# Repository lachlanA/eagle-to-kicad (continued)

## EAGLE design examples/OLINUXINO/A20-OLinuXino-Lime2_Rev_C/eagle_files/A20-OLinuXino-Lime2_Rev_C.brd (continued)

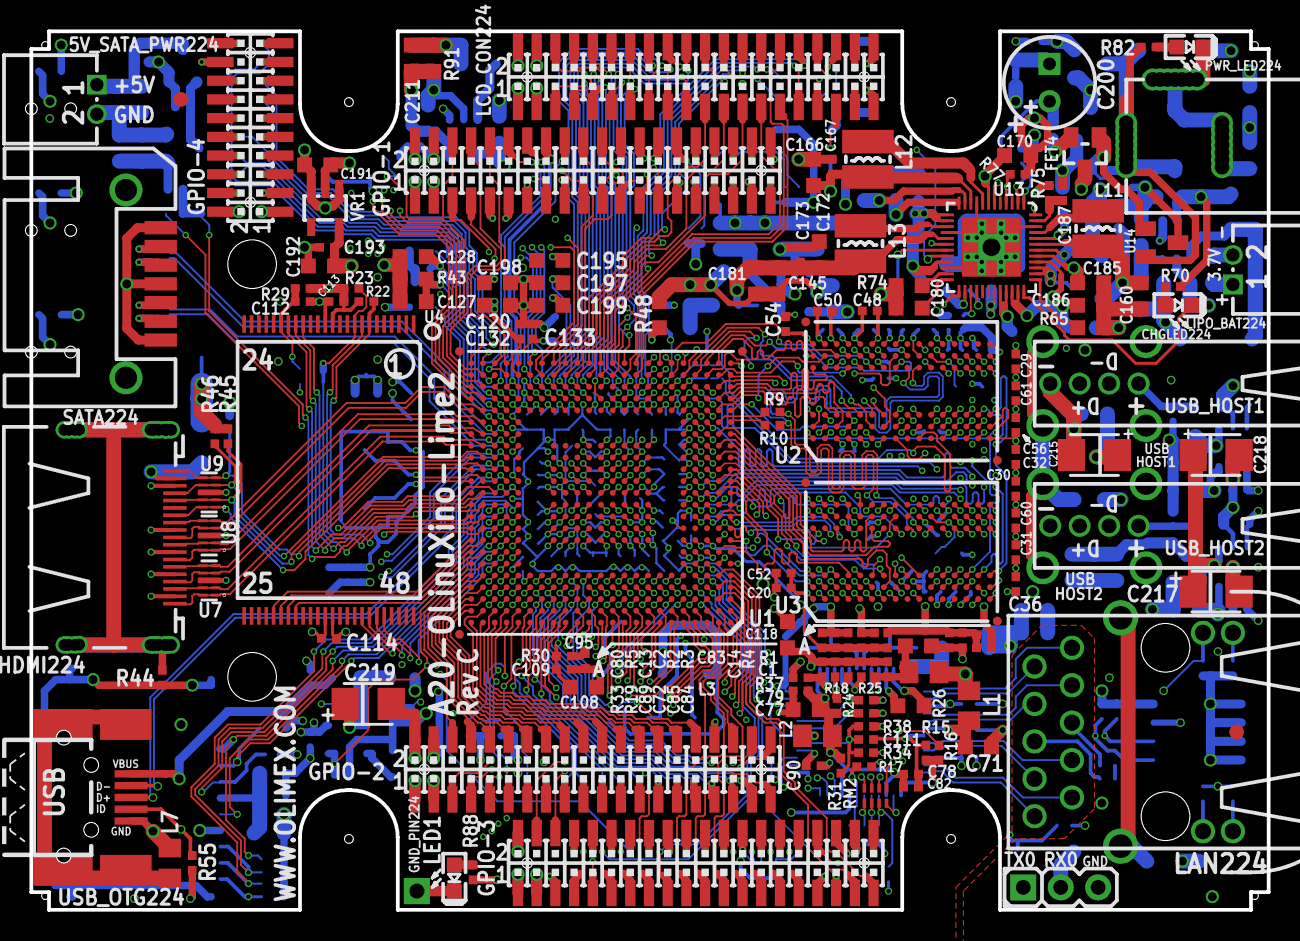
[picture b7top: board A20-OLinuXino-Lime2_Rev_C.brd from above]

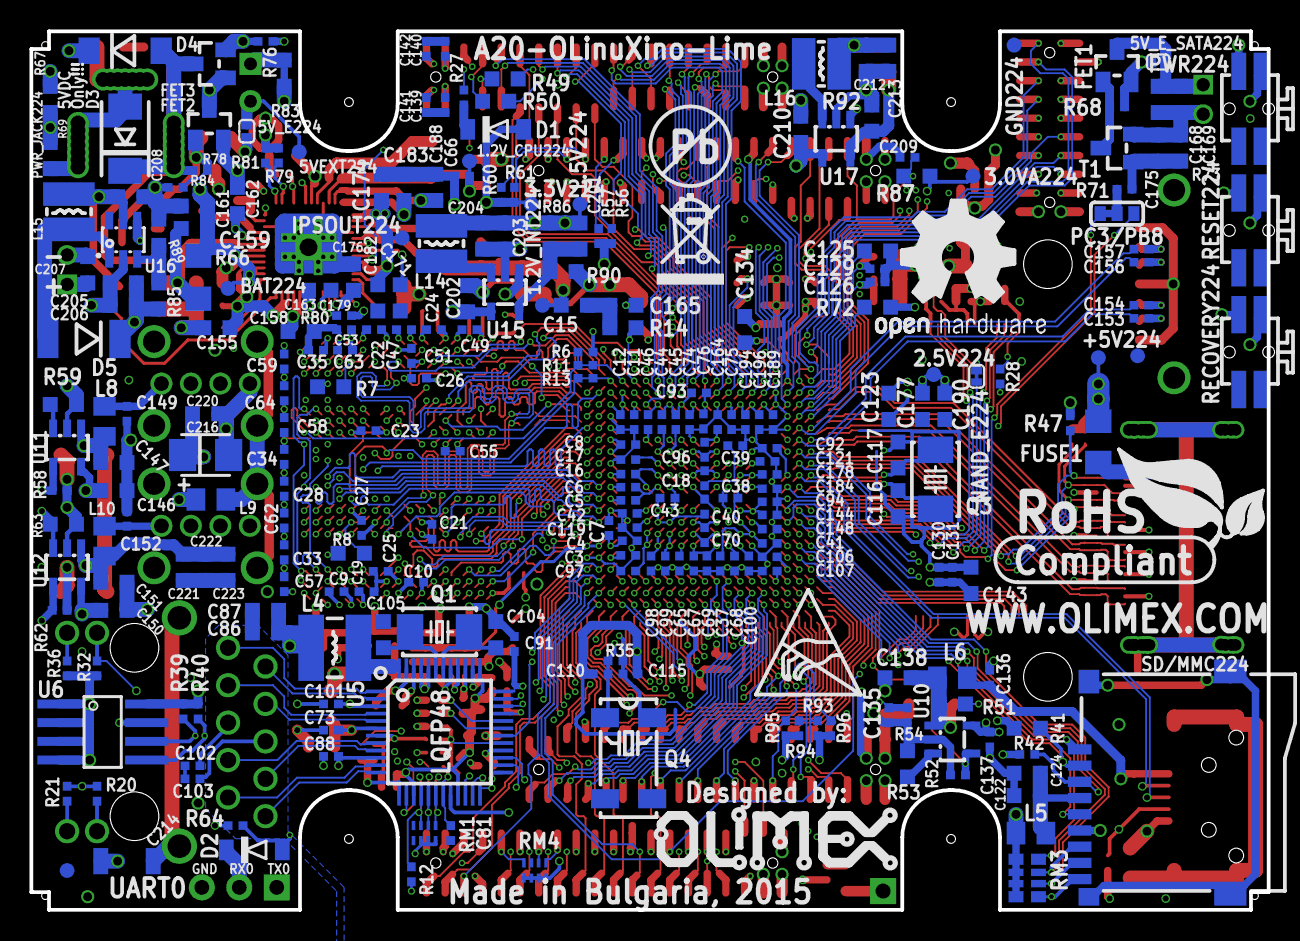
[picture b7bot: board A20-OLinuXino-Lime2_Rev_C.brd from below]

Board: 8 copper layers, 84.0 x 59.6 mm, 420 parts (274 on the bottom side), 423 nets.

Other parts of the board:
U$2: HAMMOND_1593LBK_A10_LIME
U$5: LOGO-OPENHARDWARE_8X8
U$6: OLIMEX1_V
U$9: PB
U$10: ESD_SYMBOL
U$11: RECYCLE_BIN1/8
U$12: ROHS

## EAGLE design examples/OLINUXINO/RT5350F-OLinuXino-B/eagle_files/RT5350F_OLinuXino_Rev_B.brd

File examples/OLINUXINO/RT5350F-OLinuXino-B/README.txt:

NOTE: ***** USE AT YOUR OWN RISK *****

This contains the eagle file's from OLIMEX/OLINUXINO from github, which have been Renumbered to work with KiCad
as KiCad will not work correctly with out parts reference ending in a number.
Also note the Eagle files have been converted to version 6.xx of eagle.

source of this project example is at Github address:
  OLINUXINO/HARDWARE/RT5350F/RT5350F-OLinuXino/RT5350F-OLinuXino-B/

The following is the error report. for lib extraction from the eagle sch/pcb to a eagle lbr.
which is then converted in to KiCad format.

#**** LOG Errors Start ****#
ERROR: package name:CD42(43)  Has Bad/illegal charter in it's package Alisa name!
   Package Alaise  Name:-CD42(43)
   Error Postion & Char:     (  )
   Bad charter(s) have been replaced with  '_'  This MAY FIX OR, CAUSE MORE ERROR'S! Plese fix the Alias!
ERROR: package name:CD52(53)  Has Bad/illegal charter in it's package Alisa name!
   Package Alaise  Name:-CD52(53)
   Error Postion & Char:     (  )
   Bad charter(s) have been replaced with  '_'  This MAY FIX OR, CAUSE MORE ERROR'S! Plese fix the Alias!
ERROR: package name:CD73(75)  Has Bad/illegal charter in it's package Alisa name!
   Package Alaise  Name:-CD73(75)
   Error Postion & Char:     (  )
   Bad charter(s) have been replaced with  '_'  This MAY FIX OR, CAUSE MORE ERROR'S! Plese fix the Alias!
ERROR: package name:ML26-MALE(GBH-254-SMT-26)  Has Bad/illegal charter in it's package Alisa name!
   Package Alaise  Name:-(GBH-254-SMT-26)
   Error Postion & Char: (              )
   Bad charter(s) have been replaced with  '_'  This MAY FIX OR, CAUSE MORE ERROR'S! Plese fix the Alias!
ERROR: package name:F-V50X-2X13-LF  Has Bad/illegal charter in it's package Alisa name!
   Package Alaise  Name:-F-V50X-2X13-LF(FEMALE)
   Error Postion & Char:               (      )
   Bad charter(s) have been replaced with  '_'  This MAY FIX OR, CAUSE MORE ERROR'S! Plese fix the Alias!

#**** LOG Warning Start ****#
WARNING: Over lapping Pin(s) on SYMBOL:WIFI_RF
   Pin =GND_2

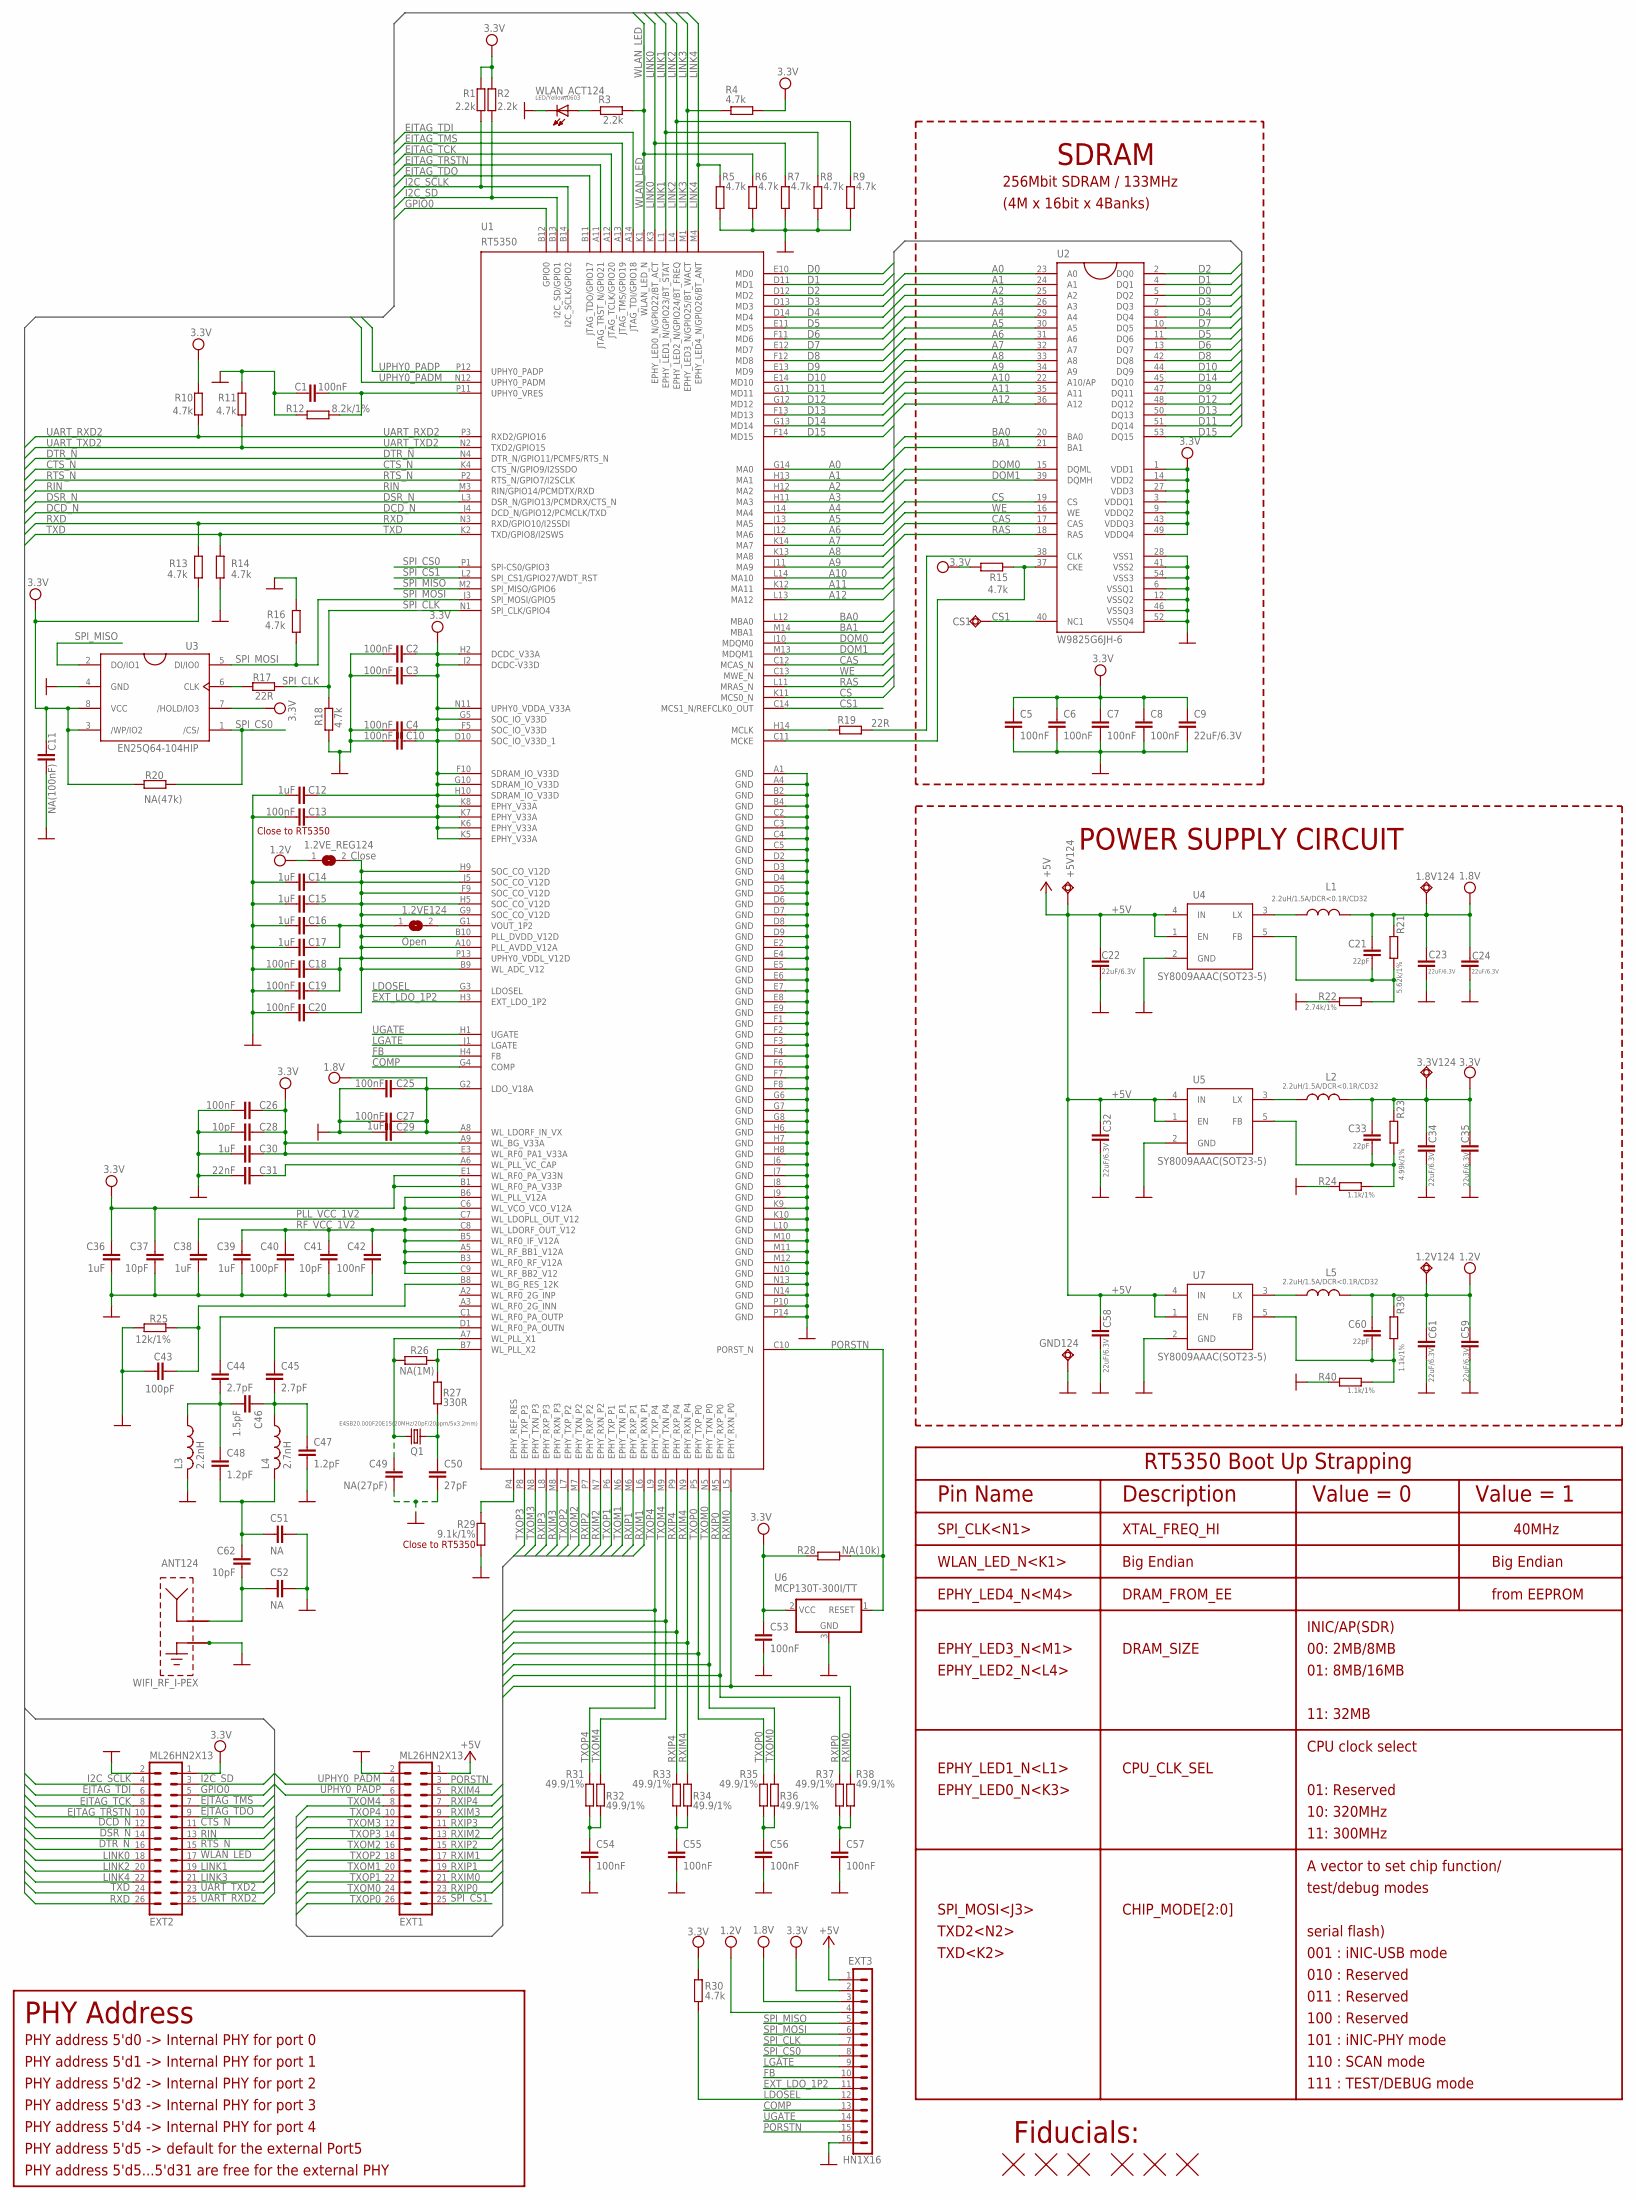
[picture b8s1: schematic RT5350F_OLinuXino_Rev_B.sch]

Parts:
1.2V124, 1.8V124: TESTPADTESTPAD_40-ROUND; TESTPAD_40-ROUND
1.2VE124: Open; SJ_1_SMALLER
1.2VE_REG124: Close; SJ_1_SMALLER
3.3V124: 3.3V; TESTPAD_40-ROUND
+5V124: TESTPADTESTPAD_40-ROUND; TESTPAD_40-ROUND
ANT124: WIFI_RF_I-PEX; WIFI_RF
C1, C2, C3, C4, C5, C6, C7, C8, C10, C13, C18, C19, C20, C25, C26, C27, C42, C53, C54, C55, C56, C57: 100nF; C0402_TI
C9, C22, C23, C24, C32, C34, C35, C58, C59, C61: 22uF/6.3V; C0603_DWS
C11: NA(100nF); C0402_TI
C12, C14, C15, C16, C17, C29, C30, C36, C38, C39: 1uF; C0603_DWS
C21, C33, C60: 22pF; C0603_DWS
C28, C37, C41, C62: 10pF; C0402_TI
C31: 22nF; C0402_TI
C40, C43: 100pF; C0402_TI
C44, C45: 2.7pF; C0402_TI
C46: 1.5pF; C0402_TI
C47, C48: 1.2pF; C0402_TI
C49: NA(27pF); C0603_DWS
C50: 27pF; C0603_DWS
C51, C52: NA; C0402_TI
CS1: TESTPADTESTPAD30/30; TESTPAD_30-ROUND
EXT1, EXT2: ML26HN2X13; HN2X13-MALE
EXT3: HN1X16
FID1, FID2, FID3, FID4, FID5, FID6: FIDUCIAL; FIDUCIAL-1X3
GND124: TESTPADTESTPAD_40-ROUND; TESTPAD_40-ROUND
L1, L2, L5: 2.2uH/1.5A/DCR<0.1R/CD32; CD32
L3: 2.2nH; L0603_5MIL_DWS
L4: 2.7nH; L0402_TI
Q1: E4SB20.000F20E15(20MHz/20pF/20ppm/5x3.2mm); HCX-4S
R1, R2, R3: 2.2k; R0603_5MIL_DWS
R4, R5, R6, R7, R8, R9, R10, R11, R13, R14, R15, R16, R18, R30: 4.7k; R0603_5MIL_DWS
R12: 8.2k/1%; R0603_5MIL_DWS
R17, R19: 22R; R0603_5MIL_DWS
R20: NA(47k); R0603_5MIL_DWS
R21: 5.62k/1%; R0603_5MIL_DWS
R22: 2.74k/1%; R0603_5MIL_DWS
R23: 4.99k/1%; R0603_5MIL_DWS
R24, R39, R40: 1.1k/1%; R0603_5MIL_DWS
R25: 12k/1%; R0402_TI
R26: NA(1M); R0603_5MIL_DWS
R27: 330R; R0603_5MIL_DWS
R28: NA(10k); R0603_5MIL_DWS
R29: 9.1k/1%; R0603_5MIL_DWS
R31, R32, R33, R34, R35, R36, R37, R38: 49.9/1%; R0603_5MIL_DWS
U1: RT5350; TFBGA196B
U2: W9825G6JH-6; 54TSOPII
U3: EN25Q64-104HIP; SO8_ATMEL_FLASH
U4, U5, U7: SY8009AAAC(SOT23-5); SOT23-5
U6: MCP130T-300I/TT; SOT23
WLAN_ACT124: LED/Yellow/0603; LED-0603

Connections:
1.2V: 1.2VE124.1, 1.2VE_REG124.2, C14.1, C15.1, C16.1, C17.1, C18.1, C19.1, C20.1, U1.A10 (PLL_AVDD_V12A), U1.B9 (WL_ADC_V12), U1.B10 (PLL_DVDD_V12D), U1.F9 (SOC_CO_V12D), U1.G9 (SOC_CO_V12D), U1.H5 (SOC_CO_V12D), U1.H9 (SOC_CO_V12D), U1.J5 (SOC_CO_V12D), U1.P13 (UPHY0_VDDL_V12D)
+5V: +5V124.1, C22.1, C32.1, C58.1, EXT1.1, EXT3.1, U4.1 (EN), U4.4 (IN), U5.1 (EN), U5.4 (IN), U7.1 (EN), U7.4 (IN)
A0: U1.G14 (MA0), U2.23 (A0)
A1: U1.H13 (MA1), U2.24 (A1)
A2: U1.H12 (MA2), U2.25 (A2)
A3: U1.H11 (MA3), U2.26 (A3)
A4: U1.J14 (MA4), U2.29 (A4)
A5: U1.J13 (MA5), U2.30 (A5)
A6: U1.J12 (MA6), U2.31 (A6)
A7: U1.K14 (MA7), U2.32 (A7)
A8: U1.K13 (MA8), U2.33 (A8)
A9: U1.J11 (MA9), U2.34 (A9)
A10: U1.L14 (MA10), U2.22 (A10/AP)
A11: U1.K12 (MA11), U2.35 (A11)
A12: U1.L13 (MA12), U2.36 (A12)
BA0: U1.L12 (MBA0), U2.20 (BA0)
BA1: U1.M14 (MBA1), U2.21 (BA1)
CAS: U1.C12 (MCAS_N), U2.17 (CAS)
COMP: EXT3.13, U1.G4 (COMP)
CS: U1.K11 (MCS0_N), U2.19 (CS)
CS1: CS1.1, U1.C14 (MCS1_N/REFCLK0_OUT), U2.40 (NC1)
CTS_N: EXT2.11, U1.K4 (CTS_N/GPIO9/I2SSDO)
D0: U1.E10 (MD0), U2.5 (DQ2)
D1: U1.D11 (MD1), U2.4 (DQ1)
D2: U1.D12 (MD2), U2.2 (DQ0)
D3: U1.D13 (MD3), U2.7 (DQ3)
D4: U1.D14 (MD4), U2.8 (DQ4)
D5: U1.E11 (MD5), U2.11 (DQ6)
D6: U1.F11 (MD6), U2.13 (DQ7)
D7: U1.E12 (MD7), U2.10 (DQ5)
D8: U1.F12 (MD8), U2.42 (DQ8)
D9: U1.E13 (MD9), U2.47 (DQ11)
D10: U1.E14 (MD10), U2.44 (DQ9)
D11: U1.G11 (MD11), U2.51 (DQ14)
D12: U1.G12 (MD12), U2.48 (DQ12)
D13: U1.F13 (MD13), U2.50 (DQ13)
D14: U1.G13 (MD14), U2.45 (DQ10)
D15: U1.F14 (MD15), U2.53 (DQ15)
DCD_N: EXT2.12, U1.J4 (DCD_N/GPIO12/PCMCLK/TXD)
DQM0: U1.J10 (MDQM0), U2.15 (DQML)
DQM1: U1.M13 (MDQM1), U2.39 (DQMH)
DSR_N: EXT2.14, U1.L3 (DSR_N/GPIO13/PCMDRX/CTS_N)
DTR_N: EXT2.16, U1.N4 (DTR_N/GPIO11/PCMFS/RTS_N)
EJTAG_TCK: EXT2.8, U1.A12 (JTAG_TCLK/GPIO20)
EJTAG_TDI: EXT2.6, U1.A14 (JTAG_TDI/GPIO18)
EJTAG_TDO: EXT2.9, U1.B11 (JTAG_TDO/GPIO17)
EJTAG_TMS: EXT2.7, U1.A13 (JTAG_TMS/GPIO19)
EJTAG_TRSTN: EXT2.10, U1.A11 (JTAG_TRST_N/GPIO21)
EXT_LDO_1P2: EXT3.11, U1.H3 (EXT_LDO_1P2)
FB: EXT3.10, U1.H4 (FB)
GND: ANT124.GND1 (GND_1), ANT124.GND2 (GND_2), C1.2, C2.2, C3.2, C4.2, C5.2, C6.2, C7.2, C8.2, C9.2, C10.2, C11.2, C12.2, C13.2, C14.2, C15.2, C16.2, C17.2, C18.2, C19.2, C20.2, C22.2, C23.2, C24.2, C25.2, C26.2, C27.2, C28.2, C29.2, C30.2, C31.2, C32.2, C34.2, C35.2, C36.2, C37.2, C38.2, C39.2, C40.2, C41.2, C42.2, C43.2, C47.2, C49.2, C50.2, C51.2, C52.2, C53.2, C54.2, C55.2, C56.2, C57.2, C58.2, C59.2, C61.2, EXT1.2, EXT2.2, EXT3.16, GND124.1, L3.2, R5.2, R6.2, R7.2, R8.2, R9.2, R11.2, R12.2, R14.2, R16.1, R18.2, R22.2, R24.2, R25.1, R29.2, R40.2, U1.A1 (GND), U1.A4 (GND), U1.B2 (GND), U1.B4 (GND), U1.C2 (GND), U1.C3 (GND), U1.C4 (GND), U1.C5 (GND), U1.D2 (GND), U1.D3 (GND), U1.D4 (GND), U1.D5 (GND), U1.D6 (GND), U1.D7 (GND), U1.D8 (GND), U1.D9 (GND), U1.E2 (GND), U1.E4 (GND), U1.E5 (GND), U1.E6 (GND), U1.E7 (GND), U1.E8 (GND), U1.E9 (GND), U1.F1 (GND), U1.F2 (GND), U1.F3 (GND), U1.F4 (GND), U1.F6 (GND), U1.F7 (GND), U1.F8 (GND), U1.G6 (GND), U1.G7 (GND), U1.G8 (GND), U1.H6 (GND), U1.H7 (GND), U1.H8 (GND), U1.J6 (GND), U1.J7 (GND), U1.J8 (GND), U1.J9 (GND), U1.K9 (GND), U1.K10 (GND), U1.L10 (GND), U1.M10 (GND), U1.M11 (GND), U1.M12 (GND), U1.N10 (GND), U1.N13 (GND), U1.N14 (GND), U1.P10 (GND), U1.P14 (GND), U2.6 (VSSQ1), U2.12 (VSSQ2), U2.28 (VSS1), U2.41 (VSS2), U2.46 (VSSQ3), U2.52 (VSSQ4), U2.54 (VSS3), U3.4 (GND), U4.2 (GND), U5.2 (GND), U6.3 (GND), U7.2 (GND), WLAN_ACT124.C
GPIO0: EXT2.5, U1.B12 (GPIO0)
I2C_SCLK: EXT2.4, R1.1, U1.B14 (I2C_SCLK/GPIO2)
I2C_SD: EXT2.3, R2.1, U1.B13 (I2C_SD/GPIO1)
LDOSEL: EXT3.12, R30.1, U1.G3 (LDOSEL)
LGATE: EXT3.9, U1.J1 (LGATE)
LINK0: EXT2.18, R7.1, U1.K3 (EPHY_LED0_N/GPIO22/BT_ACT)
LINK1: EXT2.19, R8.1, U1.L1 (EPHY_LED1_N/GPIO23/BT_STAT)
LINK2: EXT2.20, R9.1, U1.L4 (EPHY_LED2_N/GPIO24/BT_FREQ)
LINK3: EXT2.21, R4.1, U1.M1 (EPHY_LED3_N/GPIO25/BT_WACT)
LINK4: EXT2.22, R5.1, U1.M4 (EPHY_LED4_N/GPIO26/BT_ANT)
unnamed: R17.1, U3.6 (CLK)
unnamed: C43.1, R25.2, U1.B8 (WL_BG_RES_12K)
unnamed: C44.1, U1.C1 (WL_RF0_PA_OUTP)
unnamed: C45.1, U1.D1 (WL_RF0_PA_OUTN)
unnamed: C44.2, C46.2, C48.1, L3.1
unnamed: C45.2, C46.1, C47.1, L4.1
unnamed: C48.2, C51.1, C62.1, L4.2
unnamed: R26.2, R27.1, U1.B7 (WL_PLL_X2)
unnamed: C50.1, Q1.1, R27.2
unnamed: C49.1, Q1.2, R26.1, U1.A7 (WL_PLL_X1)
unnamed: R29.1, U1.P4 (EPHY_REF_RES)
unnamed: C54.1, R31.2, R32.2
unnamed: C55.1, R33.2, R34.2
unnamed: C56.1, R35.2, R36.2
unnamed: C57.1, R37.2, R38.2
unnamed: R19.1, U1.H14 (MCLK)
unnamed: R19.2, U2.38 (CLK)
unnamed: L5.1, U7.3 (LX)
unnamed: C60.2, R39.2, R40.1, U7.5 (FB)
unnamed: L1.1, U4.3 (LX)
unnamed: C21.2, R21.2, R22.1, U4.5 (FB)
unnamed: ANT124.ANT, C52.1, C62.2
unnamed: R15.2, U1.C11 (MCKE), U2.37 (CKE)
unnamed: R3.1, WLAN_ACT124.A
unnamed: C31.1, U1.A6 (WL_PLL_VC_CAP)
unnamed: L2.1, U5.3 (LX)
unnamed: C33.2, R23.2, R24.1, U5.5 (FB)
PLL_VCC_1V2: C38.1, U1.B6 (WL_PLL_V12A), U1.C6 (WL_VCO_VCO_V12A), U1.C7 (WL_LDOPLL_OUT_V12)
PORSTN: EXT1.3, EXT3.15, R28.2, U1.C10 (PORST_N), U6.1 (RESET)
RAS: U1.L11 (MRAS_N), U2.18 (RAS)
RF_VCC_1V2: C39.1, C40.1, C41.1, C42.1, U1.A5 (WL_RF_BB1_V12A), U1.B3 (WL_RF0_RF_V12A), U1.B5 (WL_RF0_IF_V12A), U1.C8 (WL_LDORF_OUT_V12), U1.C9 (WL_RF_BB2_V12)
RIN: EXT2.13, U1.M3 (RIN/GPIO14/PCMDTX/RXD)
RTS_N: EXT2.15, U1.P2 (RTS_N/GPIO7/I2SCLK)
RXD: EXT2.26, R13.1, U1.N3 (RXD/GPIO10/I2SSDI)
RXIM0: EXT1.21, R38.1, U1.L5 (EPHY_RXN_P0)
RXIM1: EXT1.17, U1.L6 (EPHY_RXN_P1)
RXIM2: EXT1.13, U1.N7 (EPHY_RXN_P2)
RXIM3: EXT1.9, U1.M8 (EPHY_RXN_P3)
RXIM4: EXT1.5, R34.1, U1.N9 (EPHY_RXN_P4)
RXIP0: EXT1.23, R37.1, U1.M5 (EPHY_RXP_P0)
RXIP1: EXT1.19, U1.M6 (EPHY_RXP_P1)
RXIP2: EXT1.15, U1.P7 (EPHY_RXP_P2)
RXIP3: EXT1.11, U1.L8 (EPHY_RXP_P3)
RXIP4: EXT1.7, R33.1, U1.P9 (EPHY_RXP_P4)
SPI_CLK: EXT3.7, R17.2, R18.1, U1.N1 (SPI_CLK/GPIO4)
SPI_CS0: EXT3.8, R20.2, U1.P1 (SPI-CS0/GPIO3), U3.1 (/CS/)
SPI_CS1: EXT1.25, U1.L2 (SPI_CS1/GPIO27/WDT_RST)
SPI_MISO: EXT3.5, U1.M2 (SPI_MISO/GPIO6), U3.2 (DO/IO1)
SPI_MOSI: EXT3.6, R16.2, U1.J3 (SPI_MOSI/GPIO5), U3.5 (DI/IO0)
TXD: EXT2.24, R14.1, U1.K2 (TXD/GPIO8/I2SWS)
TXOM0: EXT1.24, R36.1, U1.N5 (EPHY_TXN_P0)
TXOM1: EXT1.20, U1.N6 (EPHY_TXN_P1)
TXOM2: EXT1.16, U1.M7 (EPHY_TXN_P2)
TXOM3: EXT1.12, U1.N8 (EPHY_TXN_P3)
TXOM4: EXT1.8, R32.1, U1.M9 (EPHY_TXN_P4)
TXOP0: EXT1.26, R35.1, U1.P5 (EPHY_TXP_P0)
TXOP1: EXT1.22, U1.P6 (EPHY_TXP_P1)
TXOP2: EXT1.18, U1.L7 (EPHY_TXP_P2)
TXOP3: EXT1.14, U1.P8 (EPHY_TXP_P3)
TXOP4: EXT1.10, R31.1, U1.L9 (EPHY_TXP_P4)
UART_RXD2: EXT2.25, R10.1, U1.P3 (RXD2/GPIO16)
UART_TXD2: EXT2.23, R11.1, U1.N2 (TXD2/GPIO15)
UGATE: EXT3.14, U1.H1 (UGATE)
UPHY0_PADM: EXT1.4, U1.N12 (UPHY0_PADM)
UPHY0_PADP: EXT1.6, U1.P12 (UPHY0_PADP)
UPHY0_VRES: C1.1, R12.1, U1.P11 (UPHY0_VRES)
VCC: 3.3V124.1, C2.1, C3.1, C4.1, C5.1, C6.1, C7.1, C8.1, C9.1, C10.1, C11.1, C12.1, C13.1, C26.1, C28.1, C30.1, C33.1, C34.1, C35.1, C36.1, C37.1, C53.1, EXT2.1, EXT3.2, L2.2, R1.2, R2.2, R4.2, R10.2, R13.2, R15.1, R20.1, R23.1, R28.1, R30.2, U1.A9 (WL_BG_V33A), U1.B1 (WL_RF0_PA_V33P), U1.D10 (SOC_IO_V33D_1), U1.E1 (WL_RF0_PA_V33N), U1.E3 (WL_RF0_PA1_V33A), U1.F5 (SOC_IO_V33D), U1.F10 (SDRAM_IO_V33D), U1.G5 (SOC_IO_V33D), U1.G10 (SDRAM_IO_V33D), U1.H2 (DCDC_V33A), U1.H10 (SDRAM_IO_V33D), U1.J2 (DCDC-V33D), U1.K5 (EPHY_V33A), U1.K6 (EPHY_V33A), U1.K7 (EPHY_V33A), U1.K8 (EPHY_V33A), U1.N11 (UPHY0_VDDA_V33A), U2.1 (VDD1), U2.3 (VDDQ1), U2.9 (VDDQ2), U2.14 (VDD2), U2.27 (VDD3), U2.43 (VDDQ3), U2.49 (VDDQ4), U3.3 (/WP/IO2), U3.7 (/HOLD/IO3), U3.8 (VCC), U6.2 (VCC)
VEE: 1.2V124.1, 1.2VE_REG124.1, C59.1, C60.1, C61.1, EXT3.4, L5.2, R39.1
VOUT_1P2: 1.2VE124.2, U1.G1 (VOUT_1P2)
VPP: 1.8V124.1, C21.1, C23.1, C24.1, C25.1, C27.1, C29.1, EXT3.3, L1.2, R21.1, U1.A8 (WL_LDORF_IN_VX), U1.G2 (LDO_V18A)
WE: U1.C13 (MWE_N), U2.16 (WE)
WLAN_LED: EXT2.17, R3.2, R6.1, U1.K1 (WLAN_LED_N)

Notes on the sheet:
PHY address 5'd0 -> Internal PHY for port 0
PHY address 5'd1 -> Internal PHY for port 1
PHY address 5'd2 -> Internal PHY for port 2
PHY address 5'd3 -> Internal PHY for port 3
PHY address 5'd4 -> Internal PHY for port 4
PHY address 5'd5 -> default for the external Port5
PHY address 5'd5...5'd31 are free for the external PHY
Close to RT5350
SDRAM
256Mbit SDRAM / 133MHz
(4M x 16bit x 4Banks)
Fiducials:
POWER SUPPLY CIRCUIT
RT5350 Boot Up Strapping
Pin Name
Description
Value = 0
Value = 1
SPI_CLK<N1>
XTAL_FREQ_HI
40MHz
WLAN_LED_N<K1>
Big Endian
EPHY_LED4_N<M4>
DRAM_FROM_EE
from EEPROM
EPHY_LED3_N<M1>
EPHY_LED2_N<L4>
DRAM_SIZE
INIC/AP(SDR)
00: 2MB/8MB
01: 8MB/16MB
11: 32MB
EPHY_LED1_N<L1>
EPHY_LED0_N<K3>
CPU_CLK_SEL
CPU clock select
01: Reserved
10: 320MHz
11: 300MHz

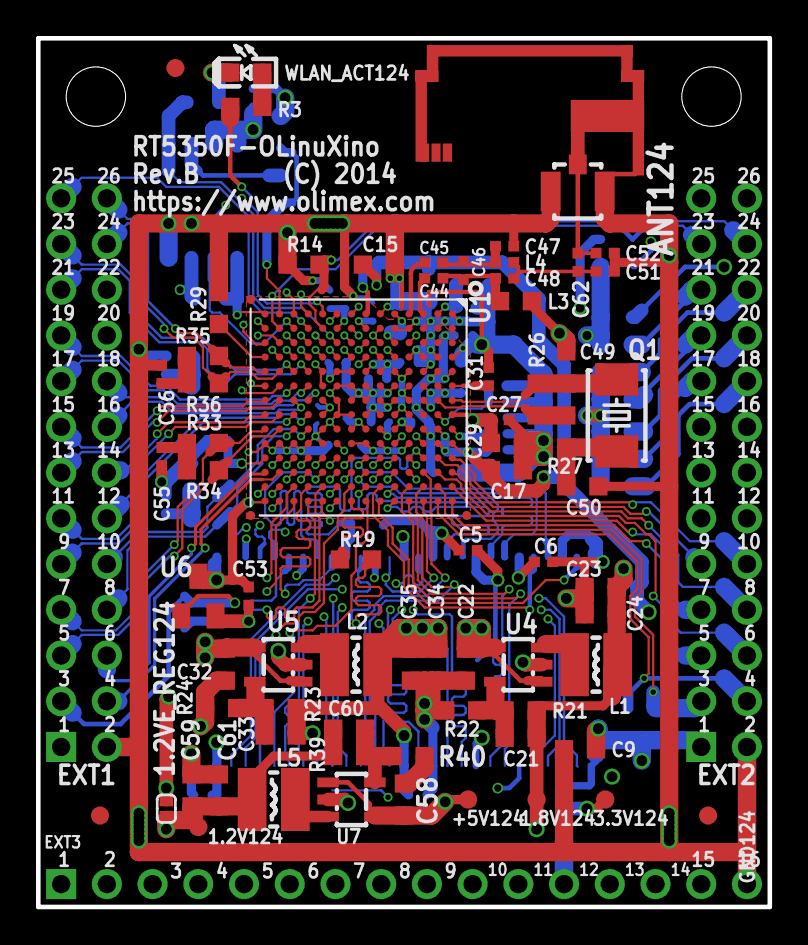
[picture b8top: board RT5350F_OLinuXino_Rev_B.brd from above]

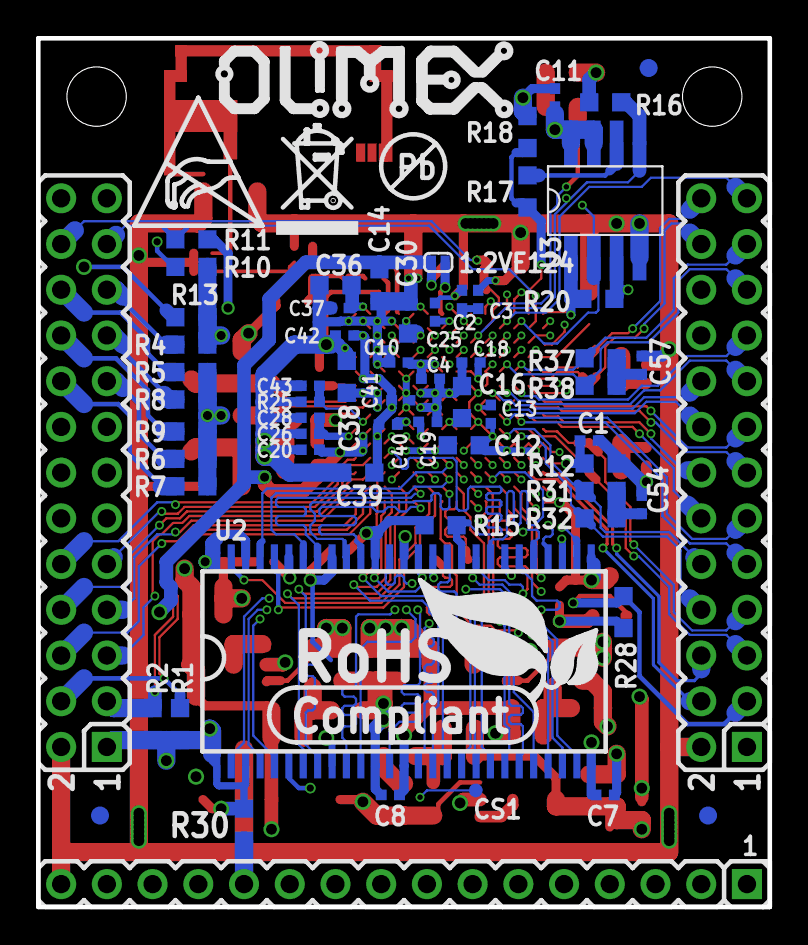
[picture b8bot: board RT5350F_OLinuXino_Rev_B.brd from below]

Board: 4 copper layers, 40.6 x 48.3 mm, 139 parts (68 on the bottom side), 133 nets.

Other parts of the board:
U$3: PB_SMALL
U$8: RECYCLE_BIN1/8
U$9: ROHS
U$10: OLIMEX1_V
U$11: ESD_SYMBOL

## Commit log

2014-07-26 try fix for module part number/value
2014-07-26 Add comment about zero size squ pad fix
2014-07-27 Fix line width of text, so it use's the size from eagle to get the correct size for kicad module text
    Fix the text from ealge, so only >NAME and >VALUE are use for prfix and value
    in Kicad, all other text is put in T2-Tx, so now we don't lose the extra text from eagle !
2014-07-27 remove some comment out test code
2014-07-27 Remove more test code. Lachlan.
2014-07-30 more fix's and addtions
2014-07-30 Continue clean up, for relase
2014-07-31 Clean up coments, add link to the github site. Add GPL V2 LICENSE.txt files
2014-07-31 fix up README.md formating.. try 1
2014-07-31 more doc's clean up, and better README.md file with html formating added.
2014-08-03 Add sch convert
2014-08-04 Fix size conversion factor
2014-08-04 Fix text on more the one line, Add version 2 of sch, add muliti part's
2014-08-13 eagle2kicad_sch.ulp Now dos mulite parts, where sch dos not use all the parts.
2014-08-14 Fix free text bug in lib conversion. Add lib list to end of sch conversion message.
2014-08-25 Change defalt options eagle-lbr2kicad-1.0.ulp fix some formating bugs.
    Chang/Fix's for eagle2kicad_sch.ulp
    fix number of bug's for format output.
    add better F0 name matching and order matching fix's
    lot's of fix's in fact.. eagle sch programe dos not make life easy. !!
2014-09-05 More fix's for eagle2kicad_sch.ulp Better device name matching to eagle2kicad_sch.ulp in eagle-lbr2kicad-1.0.ulp
2014-09-28 Add option, to eagle2kicad_sch.ulp to add lib prefix to part name, and foot print name
2015-01-03 add file to git.
2015-01-04 Add the file name pick for sub sheet's names.
2015-01-11 Continue adding newables mode for KICAD
2015-01-12 Continue adding muliti sheet suport.
2015-01-21 Fix the placement of text for diffant rowtations and mirring.
2015-01-21 I think all the text plancemnet problems have been fixed ! still needs more testing, plus given that KiCad has very limited control over text note's, there placement wont be that good.
2015-01-27 Fix a number of errors.
2015-01-29 Add exp-lbrs.ulp for user interface change's to eagle6xx
2015-02-01 change exp-lbrs.ulp to work with eagle6xx-sch-to-kicad-sch.ulp
2015-02-03 Fix Alais Name's, and inc Version to 1.2
2015-02-04 Fix ?, problem with eagle, add dupcate part check
2015-02-07 Add include file for eage cfg stuff, more fix's !
2015-02-09 Change include's name, fix subpart bug, when eagle dose give correct number of gate's
2015-02-15 Add new file, renumber-sheet.ulp and more fix's
2015-02-19 More clean ups.
2015-03-13 More Doc fix's and add check for exporting eagle libs.
2015-03-13 Update Readme file
2015-03-23 More doc's improvements
2015-03-26 Trying adding html formating to README.md
2015-03-26 Cotinue to figure out limits on READ.md
2015-03-26 Update README.md
    Add include file to list of used files.
2015-03-26 Ok, see how the README.md looks this time !
2015-03-26 Kep trying with markdown !
2015-03-26 one more time !
2015-03-26 Kepp fixing ..
2015-03-26 yup..
2015-03-26 rev forever !
2015-03-26 Remove tracking of 2 ulp files which are not used
2015-03-26 Update README.md
    Few more clean ups
2015-03-26 More formating clean up's and typo fix's
2015-03-26 More fix's
2015-03-28 Update README.md
    fix some my typoe's
2015-03-28 Update README.md
    Better explain save AS
2015-03-28 Update README.md
    Add more to save as.
2015-03-29 Update README.md
    Add more doc's for net-list conversion.
2015-03-29 Update README.md
    More typo fix's
2015-03-29 Update README.md
    Fix header
2015-03-29 More Doc fix's spelling etc, and Remove warning's from the eagle6xx-sch-to-kicad-sch.ulp, untill I figure out better way of showing them.
2015-04-09 clean up's on README.md
2015-07-20 Fix / and add libname also spelling mistakes
2015-07-21 Add tempory fix for adding lib name's to part names in eagle-lbr2kicad-1.0.ulp
2015-07-24 add fix'S for some funny libs from OLINUXINO, and add first example from OLINUXINO/HARDWARE/RT5350F/RT5350F-OLinuXino/RT5350F-OLinuXino-B/
2015-07-29 Add for fix's for eagle lib export, for over lapping pad/pin/smd pads Add A20-OLinuXino-Lime2_Rev_C to the example directory
2015-07-29 remove file's not needed for example
2015-07-29 Fix directory name typo, and bold the name
2015-07-29 Add A13-OLinuXino_WIFI_Rev_G to examples
2015-08-01 Add warning's and Note's about export Eagle libs.
2015-08-01 Add fix for () in virtual parts
2015-08-01 Add warnings about flood fill, and via problems in Eagle to KiCad
2015-08-01 fix typo
2015-08-06 Upgrade Eagle/KiCad flood Fill warning
2015-08-06 take out line feed.
2015-08-23 Add fix_via_hack.ulp, more fix's to come
2015-08-23 fix ulp count
2015-08-23 More typo's fix's
2015-08-24 Fix path space problem
2015-08-25 Should work under windows now
2015-08-25 Add more info about via to pad hack
2015-08-25 More info on via pad fix
2015-08-25 more info on via/pad
2015-08-25 remove old file's before updateing with newly converted examples
2015-08-25 Add PIXHAWK example
2015-08-26 Add options for enable/disable doc and via to pad
2015-08-26 Show problem with KiCad adding / to same net, and not others with same name
2015-08-26 replace / in deice name with _, to Fix few problems
2015-08-27 Many fix's for KiCad's invistable pin to show, on virtual power pin
2015-08-30 remove () from dev name, and add Olinuxino-Nano Rev B example
2015-08-30 Add example Olinuxino micro rev D
2015-09-04 force golbale netnames on, to get around fill/net problem
2015-09-08 blind via which can't be converted to paid, docment with "X" and netname, and via number
2015-09-08 add link to github eagle-to-kicad-lib ulp, fix some errors
2015-09-08 Fix some more typo's
2015-09-08 continue clean up
2015-09-14 Add more note's about unnectoned tracks, and fill's
2015-09-16 Add some more info about version of libs suported on eagle-lbr2kicad-1.0.ulp export
2015-09-16 More docs change
2015-10-06 Unconnect via/track reporting, and much better error logging
2015-10-06 Doc update's to mach the new improvements in reporting
2015-10-06 More doc's fix
2015-10-08 reporting fix's
2015-10-08 Add check for unnconected track ends, and more reporting fixs
2015-10-08 More reporting fix's.
2015-10-08 Add reporting to conversion log.
2015-10-08 Add extra config option for passing reporting file name to other programes
2015-10-09 fix lockup
2015-10-09 More fix's for loging, and add veiw log at end
2015-10-09 Add log view at end of conversion
2015-10-09 fix ft_table path to work with spaces, remove layer's from script
2015-10-09 dont output layers command for limited version of eagle, update Build date
2015-10-09 Fix layers for limted version of Eagle.
2015-10-13 fix printing of missing prefix, when no package, inc build date
2015-10-13 fix libname in ft_tables spaces
2015-10-13 fix reporting layers, force on all the time
2015-10-14 Add RGB_LED example
2015-10-16 Make report window at end bigger aprox 1000px+
2015-10-16 Add check for symbol and package conflick when combining librarys
2015-10-19 Add reporting for fill's over Pad/smd Pads, and reporting fix's
2015-10-19 Update build date
2015-10-19 More speeling fix's and Update doc's
2015-10-20 clean up link
2015-10-20 Try video link
2015-10-21 Add better layer reporting control fix_via_hack.ulp, and Possion test video link
2015-10-22 change test video link
2015-10-23 Link to intro video, and link example to examples dirtory
2015-10-23 Try getting alignemnet working correctly
2015-10-23 typos
2015-11-17 Fix docment layers to be only 160 to 161, per new version of KiCad 4.0
2015-12-31 Add comment about working with eagle 7.xx .. maybe
2015-12-31 Add coment about global label's hack
2015-12-31 comment clean up
2015-12-31 spelling fix's
2016-02-11 Over bar works on Labels, and other Fix's
2016-03-17 added errors with files, identation and comments
    Script show problems with writing and reading files.
    Identation problems solved.
    New and better comments.
2016-05-03 Fix text layer bugs in eage-lbr2kicad..etc
2016-05-04 fix F1 to match Def in eagle-lbr2kicad, which means remove () from F1 feild
2016-05-06 fix bug where, Device has no package and more the 1 pin, update version
2016-06-11 Fix enableNetListLableFix. not being used, and update version thanks to github.com/pgroe
2016-09-29 correction shape and pad layers table
    Added the bottom solder mask to the pad layer configuration for correct production output and edit the shape layer table in order to get the whole silkscreen of the several parts on the top layer.
2016-10-07 Name devices like Eagle when combining
2016-10-07 Inc version to 2.5, and add changes
2016-12-09 change layer LUT and default layer
2016-12-10 Up dated build date
2016-12-10 Inc Version 2.7, Add cridit to Mike Tepper
2016-12-10 Minor updates
2017-02-15 Major cleanup
    I found it very difficult to follow the README due to many grammar errors. My brain would be drawn to the errors instead of following the instructions. I believe this edit clears up most of the probl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
2017-02-22 SCRIP_ULP feels like a type to me so I've changed it to SCRIPT_ULP
2017-02-23 Change 'via's' to VIAs
2017-02-23 pad's to pads
2017-02-23 More Via's fixed
2017-02-23 net's to nets
2017-02-23 ULP\'s to ULPs
2017-02-23 bug's to bugs
2017-02-23 name's to names
2017-02-23 fix's to fixes
2017-02-23 lib\'s to libs
2017-02-23 symbol's to symbols
2017-02-23 case's to cases
2017-02-23 make's to makes
2017-02-23 section's to sections
2017-02-23 layer's to layers
2017-02-23 device's and deives to devices
2017-02-23 fill's to fills
2017-02-23 plane's to planes
2017-02-23 use's to uses
2017-02-24 Fix quite a few problems
2017-02-24 Commnet out debug printer
2017-02-25 More bug fixs
2017-02-25 Add warning about schematic's wire connections
2017-02-25 Add warning about Oval pad shape
2017-02-25 Fix formating
2017-03-04 Update warnings, to make probelsm a bit clearer
2017-03-04 More warning's added to README.md
2017-03-23 Many spelling and comment fixes. No structural changes.
    I tried to make the user interface a little easier to understand.
2017-03-23 Making the user interface more clean and easier to navigate.
    Limited the amount of bold red text and added some nobr's.
2017-04-08 Fix hole conversion, spelling correction, inc version
2017-04-08 Inc build date
2017-04-09 Add to git
2017-04-20 Fix Double Quotation Marks exscaping, Inc version
2017-10-13 Fix translation of irregular pads: Fix polygon and layer translation. Fix text alignment translation. Add thanks.
2018-09-08 In 7, tweaks to suit KiCad v5.0
    and some copy-editing.
2018-09-14 couple more SCH to schematic
2019-02-23 Change firefox version to 65.0+
2019-02-23 Fix Bug where "," was not being convert to "_" in sch foot print field. LA
2019-02-23 Change first ulp file name to be easy to understand, update docs
2019-02-23 Clean up formating and doc's LA
2019-02-26 Fix bug for checking ulp are correct, preventing scripts working.
2019-04-15 Add warning about which version of KiCad to use for the conversion
2019-12-22 Update suported versions of Kicad
2019-12-22 fix version numer, so less confusing.
2020-09-28 UpDate firefox version and Kicad version
2021-02-01 Update Firefox version
2021-04-06 Update README.md
    Change Firefox version, and add note about video link
2021-10-20 Update kicad links to new domain.
    Suggesting update due to the old domain being sold off. More info at https://forum.kicad.info/t/warning-avoid-all-links-to-kicad-pcb-org-use-kicad-org/31521
2022-01-02 escape LF CR characters in text as these break the written file
